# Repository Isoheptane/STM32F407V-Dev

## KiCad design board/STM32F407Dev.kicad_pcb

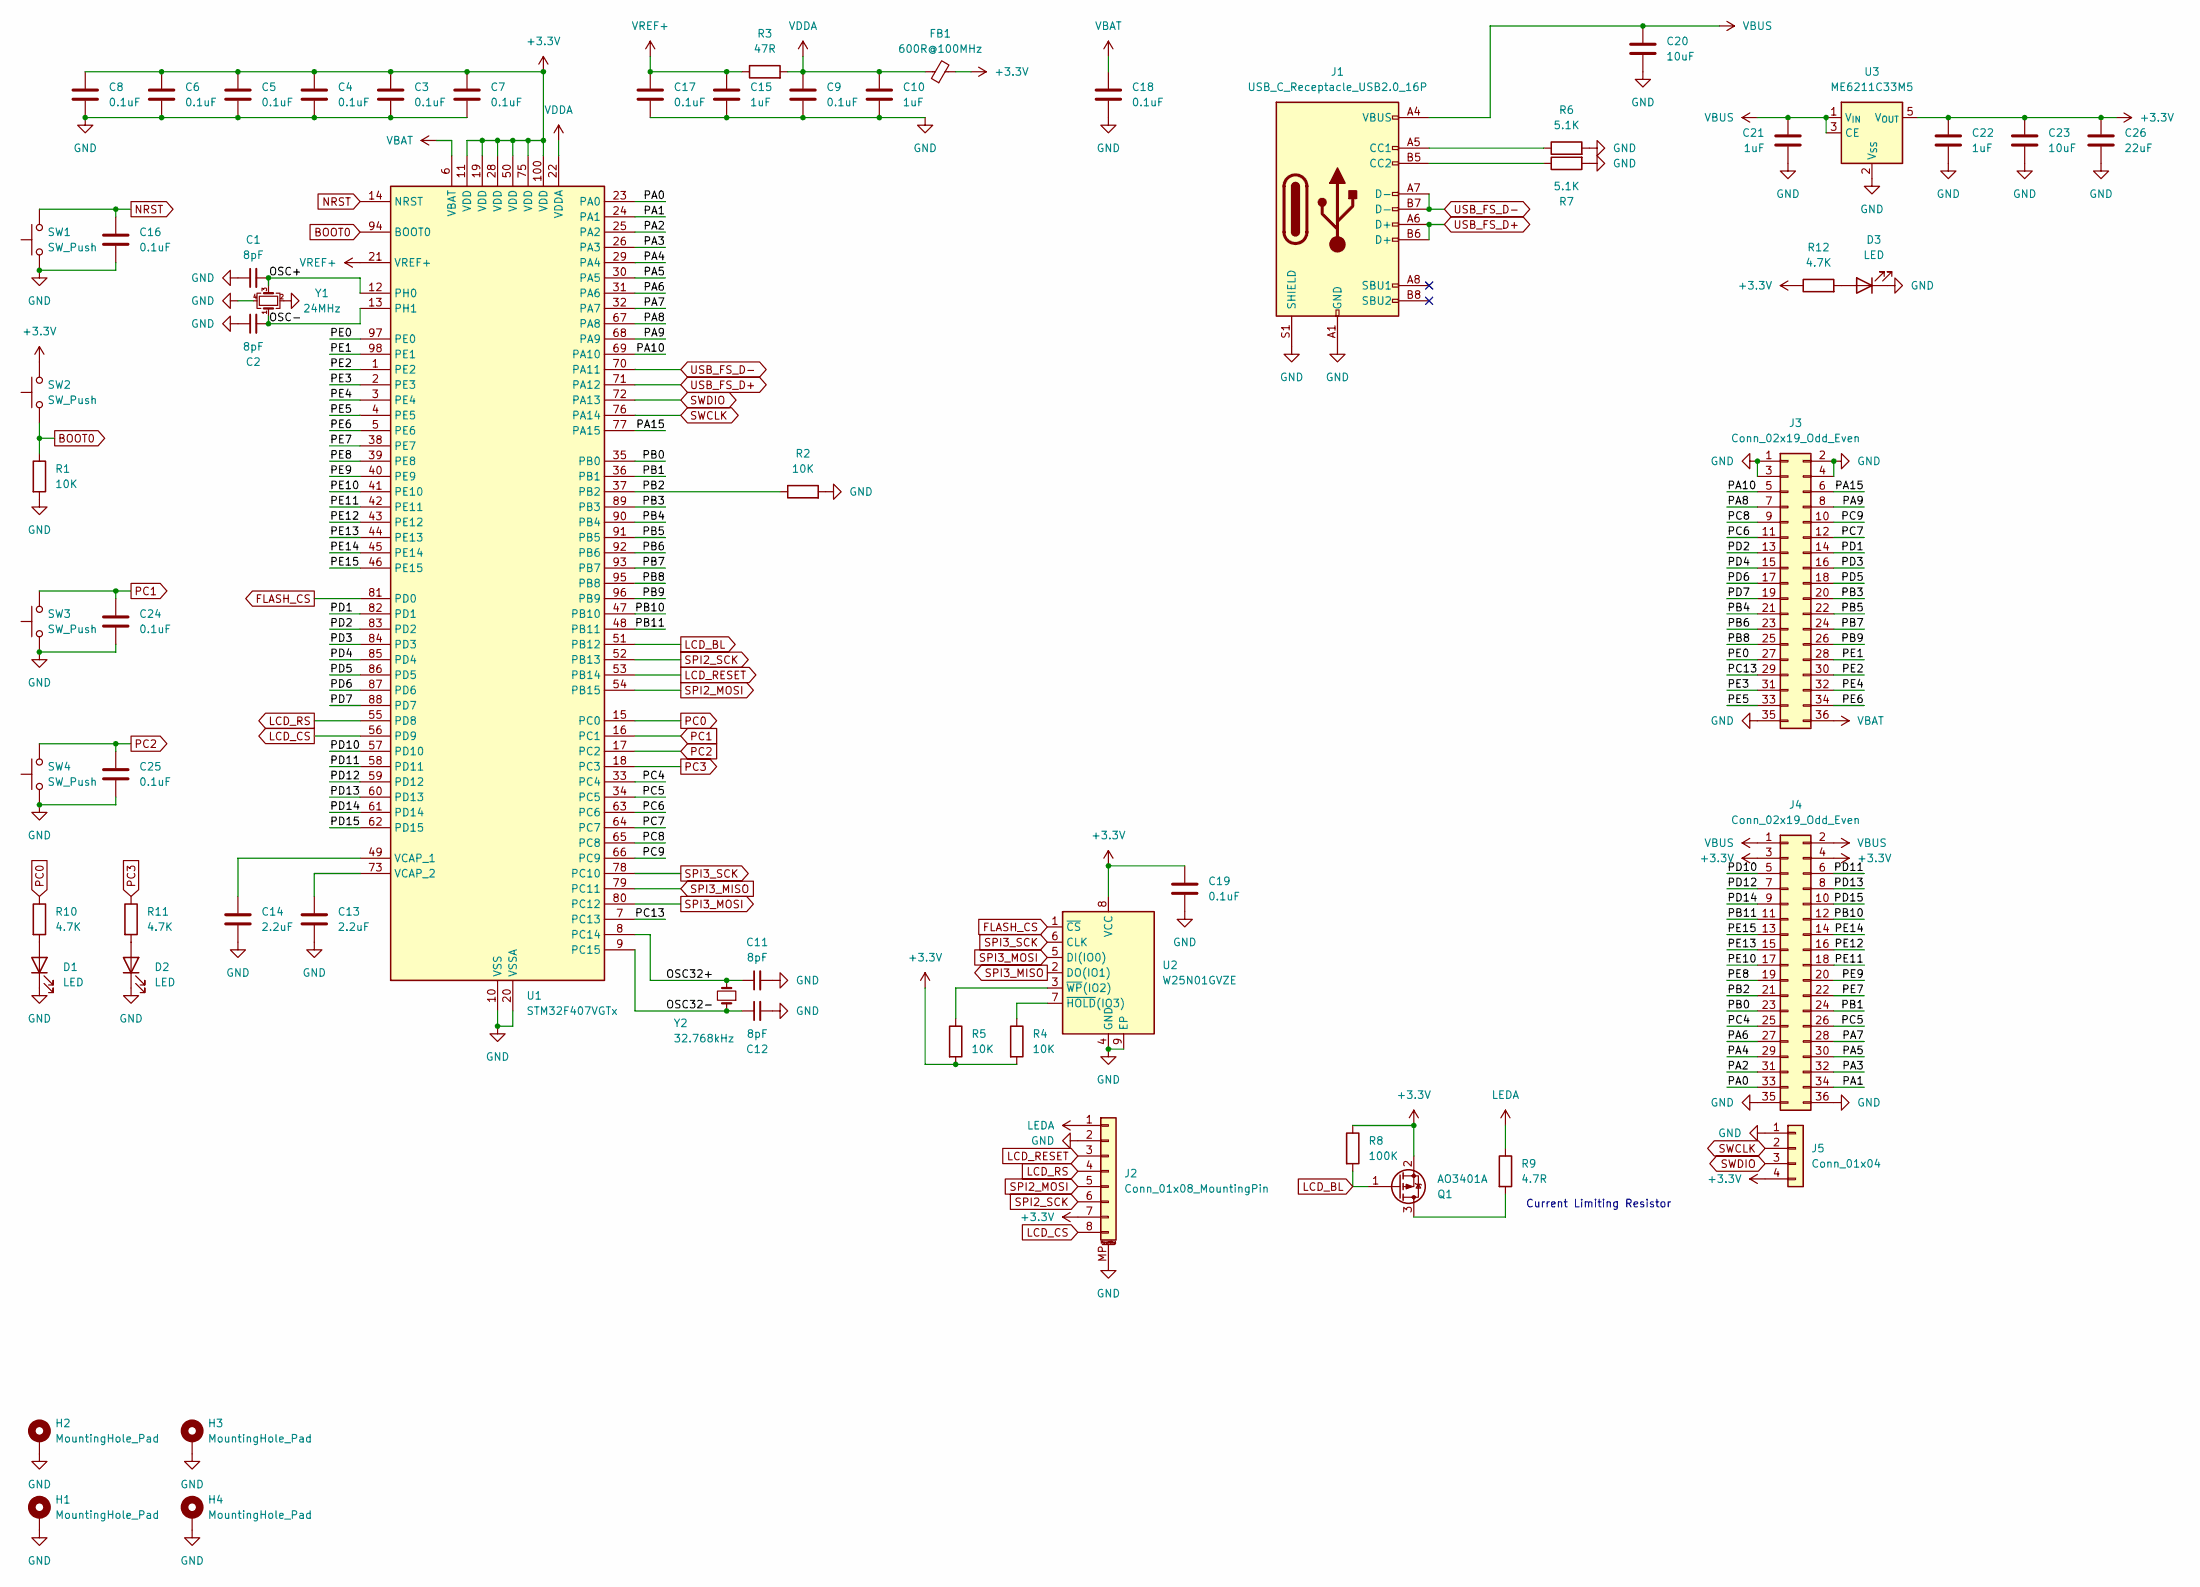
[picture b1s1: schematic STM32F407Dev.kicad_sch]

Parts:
C1, C2, C11, C12: 8pF; C_0402_1005Metric
C3, C4, C5, C6, C7, C8, C9, C16, C17, C18, C19, C24, C25: 0.1uF; C_0402_1005Metric
C10, C15: 1uF; C_0402_1005Metric
C13, C14: 2.2uF; C_0402_1005Metric
C20, C23: 10uF; C_0805_2012Metric
C21, C22: 1uF; C_0603_1608Metric
C26: 22uF; C_0805_2012Metric
D1, D2, D3: LED; LED_0603_1608Metric
FB1: 600R@100MHz; L_0603_1608Metric
H1, H2, H3, H4: MountingHole_Pad; MountingHole_2.2mm_M2_ISO7380_Pad
J1: USB_C_Receptacle_USB2.0_16P; USB_C_Receptacle_GCT_USB4105-xx-A_16P_TopMnt_Horizontal
J2: Conn_01x08_MountingPin; Hirose_FH12-8S-0.5SH_1x08-1MP_P0.50mm_Horizontal
J3, J4: Conn_02x19_Odd_Even; PinHeader_2x18_P2.54mm_Vertical
J5: Conn_01x04; PinHeader_1x04_P2.54mm_Vertical
Q1: AO3401A; SOT-23
R1, R2, R4, R5: 10K; R_0402_1005Metric
R3: 47R; R_0402_1005Metric
R6, R7: 5.1K; R_0402_1005Metric
R8: 100K; R_0402_1005Metric
R9: 4.7R; R_0402_1005Metric
R10, R11, R12: 4.7K; R_0402_1005Metric
SW1, SW2, SW3, SW4: SW_Push; SW_SPST_PTS810
U1: STM32F407VGTx; LQFP-100_14x14mm_P0.5mm
U2: W25N01GVZE; WSON-8-1EP_8x6mm_P1.27mm_EP3.4x4.3mm_WidePin
U3: ME6211C33M5; SOT-23-5
Y1: 24MHz; Crystal_SMD_3225-4Pin_3.2x2.5mm
Y2: 32.768kHz; Crystal_SMD_3215-2Pin_3.2x1.5mm

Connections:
+3.3V: C3.1, C4.1, C5.1, C6.1, C7.1, C8.1, C19.1, C22.1, C23.1, C26.1, FB1.2, J2.7, J4.3, J4.4, J5.4, Q1.2 (S), R4.2, R5.2, R8.1, R12.1, SW2.2, U1.11 (VDD), U1.19 (VDD), U1.28 (VDD), U1.50 (VDD), U1.75 (VDD), U1.100 (VDD), U2.8 (VCC), U3.5 (V_{OUT})
/OSC32+: C11.1, U1.8 (PC14), Y2.2
/OSC32-: C12.1, U1.9 (PC15), Y2.1
/OSC+: C1.2, U1.12 (PH0), Y1.3
/OSC-: C2.2, U1.13 (PH1), Y1.1
/PA0: J4.33, U1.23 (PA0)
/PA1: J4.34, U1.24 (PA1)
/PA2: J4.31, U1.25 (PA2)
/PA3: J4.32, U1.26 (PA3)
/PA4: J4.29, U1.29 (PA4)
/PA5: J4.30, U1.30 (PA5)
/PA6: J4.27, U1.31 (PA6)
/PA7: J4.28, U1.32 (PA7)
/PA8: J3.7, U1.67 (PA8)
/PA9: J3.8, U1.68 (PA9)
/PA10: J3.5, U1.69 (PA10)
/PA15: J3.6, U1.77 (PA15)
/PB0: J4.23, U1.35 (PB0)
/PB1: J4.24, U1.36 (PB1)
/PB2: J4.21, R2.1, U1.37 (PB2)
/PB3: J3.20, U1.89 (PB3)
/PB4: J3.21, U1.90 (PB4)
/PB5: J3.22, U1.91 (PB5)
/PB6: J3.23, U1.92 (PB6)
/PB7: J3.24, U1.93 (PB7)
/PB8: J3.25, U1.95 (PB8)
/PB9: J3.26, U1.96 (PB9)
/PB10: J4.12, U1.47 (PB10)
/PB11: J4.11, U1.48 (PB11)
/PC4: J4.25, U1.33 (PC4)
/PC5: J4.26, U1.34 (PC5)
/PC6: J3.11, U1.63 (PC6)
/PC7: J3.12, U1.64 (PC7)
/PC8: J3.9, U1.65 (PC8)
/PC9: J3.10, U1.66 (PC9)
/PC13: J3.29, U1.7 (PC13)
/PD1: J3.14, U1.82 (PD1)
/PD2: J3.13, U1.83 (PD2)
/PD3: J3.16, U1.84 (PD3)
/PD4: J3.15, U1.85 (PD4)
/PD5: J3.18, U1.86 (PD5)
/PD6: J3.17, U1.87 (PD6)
/PD7: J3.19, U1.88 (PD7)
/PD10: J4.5, U1.57 (PD10)
/PD11: J4.6, U1.58 (PD11)
/PD12: J4.7, U1.59 (PD12)
/PD13: J4.8, U1.60 (PD13)
/PD14: J4.9, U1.61 (PD14)
/PD15: J4.10, U1.62 (PD15)
/PE0: J3.27, U1.97 (PE0)
/PE1: J3.28, U1.98 (PE1)
/PE2: J3.30, U1.1 (PE2)
/PE3: J3.31, U1.2 (PE3)
/PE4: J3.32, U1.3 (PE4)
/PE5: J3.33, U1.4 (PE5)
/PE6: J3.34, U1.5 (PE6)
/PE7: J4.22, U1.38 (PE7)
/PE8: J4.19, U1.39 (PE8)
/PE9: J4.20, U1.40 (PE9)
/PE10: J4.17, U1.41 (PE10)
/PE11: J4.18, U1.42 (PE11)
/PE12: J4.16, U1.43 (PE12)
/PE13: J4.15, U1.44 (PE13)
/PE14: J4.14, U1.45 (PE14)
/PE15: J4.13, U1.46 (PE15)
BOOT0: R1.1, SW2.1, U1.94 (BOOT0)
FLASH_CS: U1.81 (PD0), U2.1 (~CS)
GND: C1.1, C2.1, C3.2, C4.2, C5.2, C6.2, C7.2, C8.2, C9.2, C10.2, C11.2, C12.2, C13.2, C14.2, C15.2, C16.2, C17.2, C18.2, C19.2, C20.2, C21.2, C22.2, C23.2, C24.2, C25.2, C26.2, D1.1 (K), D2.1 (K), D3.1 (K), H1.1, H2.1, H3.1, H4.1, J1.A1 (GND), J1.A12 (GND), J1.B1 (GND), J1.B12 (GND), J1.S1 (SHIELD), J2.2, J2.MP (MountPin), J3.1, J3.2, J3.3, J3.4, J3.35, J4.35, J4.36, J5.1, R1.2, R2.2, R6.2, R7.2, SW1.1, SW3.1, SW4.1, U1.10 (VSS), U1.20 (VSSA), U1.27 (VSS), U1.74 (VSS), U1.99 (VSS), U2.4 (GND), U2.9 (EP), U3.2 (V_{SS}), Y1.2, Y1.4
LCD_BL: Q1.1 (G), R8.2, U1.51 (PB12)
LCD_CS: J2.8, U1.56 (PD9)
LCD_RESET: J2.3, U1.53 (PB14)
LCD_RS: J2.4, U1.55 (PD8)
LEDA: J2.1, R9.1
NRST: C16.1, SW1.2, U1.14 (NRST)
unnamed: D1.2 (A), R10.2
unnamed: D2.2 (A), R11.2
unnamed: D3.2 (A), R12.2
unnamed: J1.A5 (CC1), R6.1
unnamed: J1.B5 (CC2), R7.1
unnamed: Q1.3 (D), R9.2
unnamed: C14.1, U1.49 (VCAP_1)
unnamed: C13.1, U1.73 (VCAP_2)
unnamed: R4.1, U2.7 (~HOLD(IO3))
unnamed: R5.1, U2.3 (~WP(IO2))
PC0: R10.1, U1.15 (PC0)
PC1: C24.1, SW3.2, U1.16 (PC1)
PC2: C25.1, SW4.2, U1.17 (PC2)
PC3: R11.1, U1.18 (PC3)
SPI2_MOSI: J2.5, U1.54 (PB15)
SPI2_SCK: J2.6, U1.52 (PB13)
SPI3_MISO: U1.79 (PC11), U2.2 (DO(IO1))
SPI3_MOSI: U1.80 (PC12), U2.5 (DI(IO0))
SPI3_SCK: U1.78 (PC10), U2.6 (CLK)
SWCLK: J5.2, U1.76 (PA14)
SWDIO: J5.3, U1.72 (PA13)
USB_FS_D+: J1.A6 (D+), J1.B6 (D+), U1.71 (PA12)
USB_FS_D-: J1.A7 (D-), J1.B7 (D-), U1.70 (PA11)
VBAT: C18.1, J3.36, U1.6 (VBAT)
VBUS: C20.1, C21.1, J1.A4 (VBUS), J1.A9 (VBUS), J1.B4 (VBUS), J1.B9 (VBUS), J4.1, J4.2, U3.1 (V_{IN}), U3.3 (CE)
VDDA: C9.1, C10.1, FB1.1, R3.2, U1.22 (VDDA)
VREF+: C15.1, C17.1, R3.1, U1.21 (VREF+)

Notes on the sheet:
Current Limiting Resistor

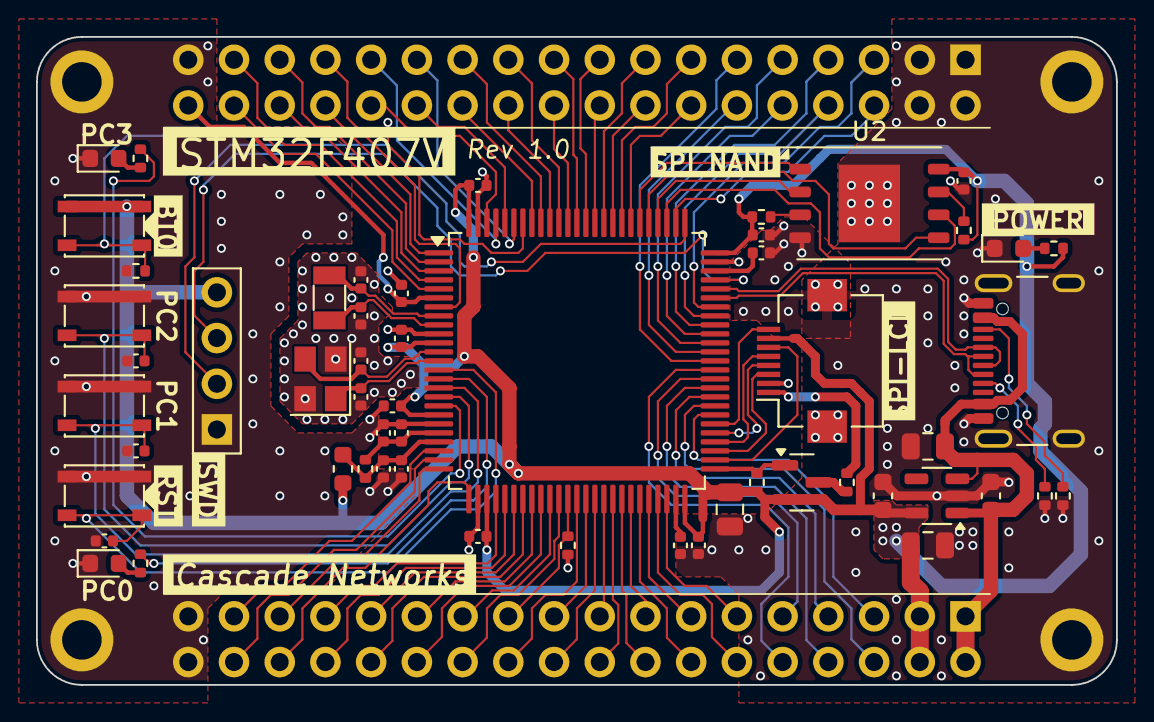
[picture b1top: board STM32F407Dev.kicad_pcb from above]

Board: 2 copper layers, 60.0 x 36.0 mm, 61 parts (0 on the bottom side), 101 nets.

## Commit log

2024-11-13 Update STM32F407Dev Board Design Files
2024-11-13 Board: Move Board Design Files
2025-10-26 Update STM32F407 file, delete backup and lock
2025-10-26 Add CERN-OHL-W License
